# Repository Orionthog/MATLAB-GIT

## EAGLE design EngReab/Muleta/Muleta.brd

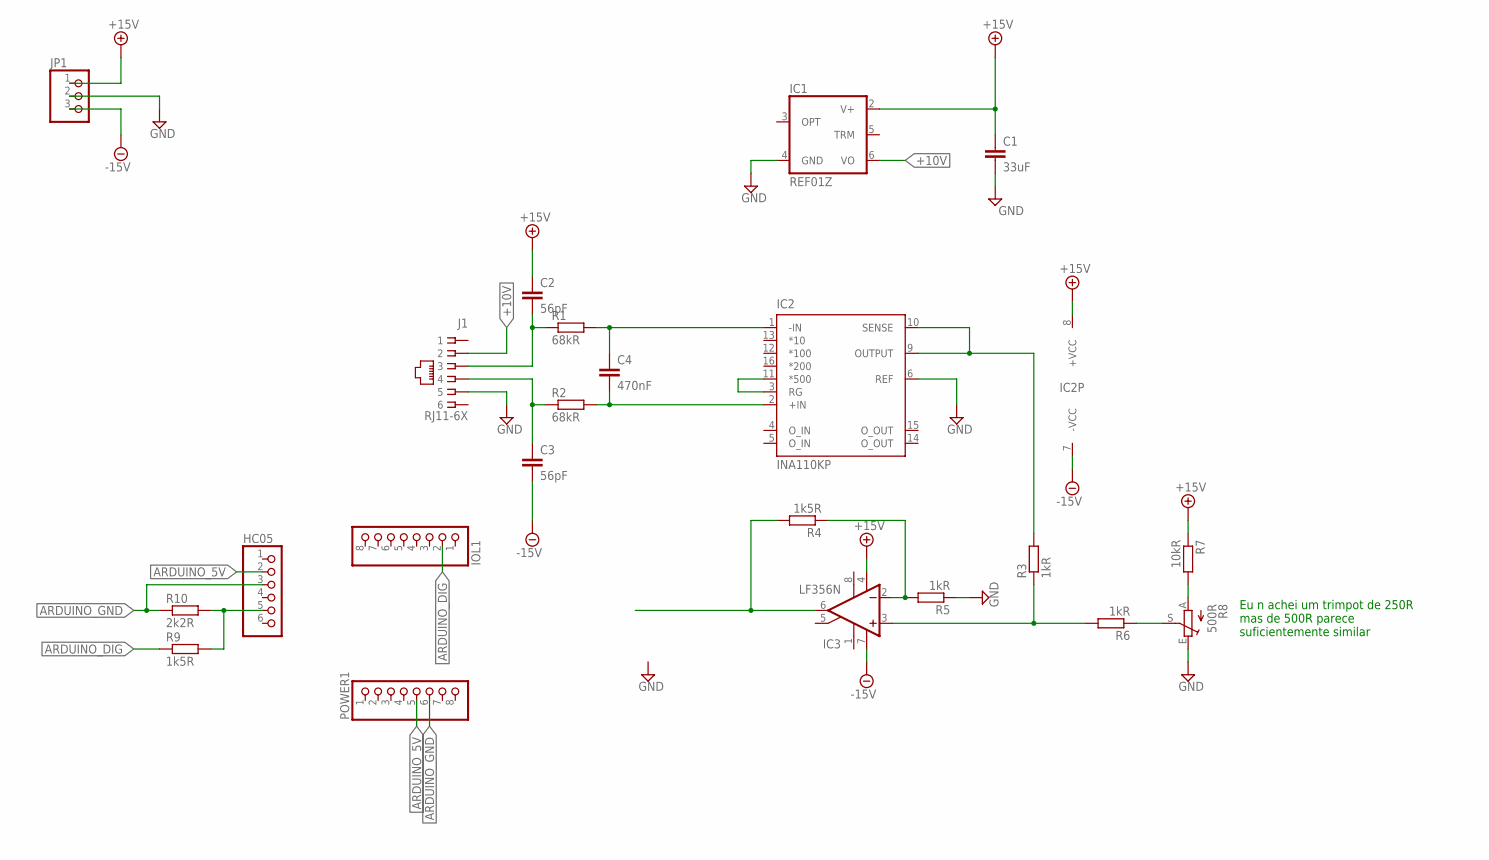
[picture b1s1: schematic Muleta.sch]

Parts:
C1: 33uF; C2.5-3
C2, C3: 56pF; C5B2.5
C4: 470nF; C5B2.5
HC05: PINHD-1X6/90; 1X06/90
IC1: REF01Z; DIL08
IC2: INA110KP; DIL16
IC3: LF356N; DIL08
IOL1: PINHD-1X8; 1X08
J1: RJ11-6X; RJ11-NO_SHIELD
JP1: PINHD-1X3; 1X03
POWER1: PINHD-1X8; 1X08
R1, R2: 68kR; 0207/7
R3, R5, R6: 1kR; 0207/7
R4, R9: 1k5R; 0207/7
R7: 10kR; 0207/7
R8: 500R; B64Y
R10: 2k2R; 0207/7

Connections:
+10V: IC1.6 (VO), J1.2
+15V: C1.1, C2.1, IC1.2 (V+), IC2.8 (+VCC), IC3.4 (V-), JP1.1, R7.1
-15V: C3.2, IC2.7 (-VCC), IC3.7 (V+), JP1.3
ARDUINO_5V: HC05.2, POWER1.5
ARDUINO_DIG: IOL1.2, R9.1
ARDUINO_GND: HC05.3, POWER1.6, R10.1
GND: C1.2, IC1.4 (GND), IC2.6 (REF), J1.5, JP1.2, R5.1, R8.E
unnamed: R6.1, R8.S
unnamed: R7.2, R8.A
unnamed: C3.1, J1.4, R2.1
unnamed: C2.2, J1.3, R1.1
unnamed: C4.2, IC2.2 (+IN), R2.2
unnamed: C4.1, IC2.1 (-IN), R1.2
unnamed: IC2.3 (RG), IC2.11 (*500)
unnamed: IC2.9 (OUTPUT), IC2.10 (SENSE), R3.2
unnamed: IC3.6 (OUT), R4.2
unnamed: IC3.2 (-IN), R4.1, R5.2
unnamed: IC3.3 (+IN), R3.1, R6.2
unnamed: HC05.5, R9.2, R10.2

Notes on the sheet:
Eu n achei um trimpot de 250R mas de 500R parece suficientemente similar

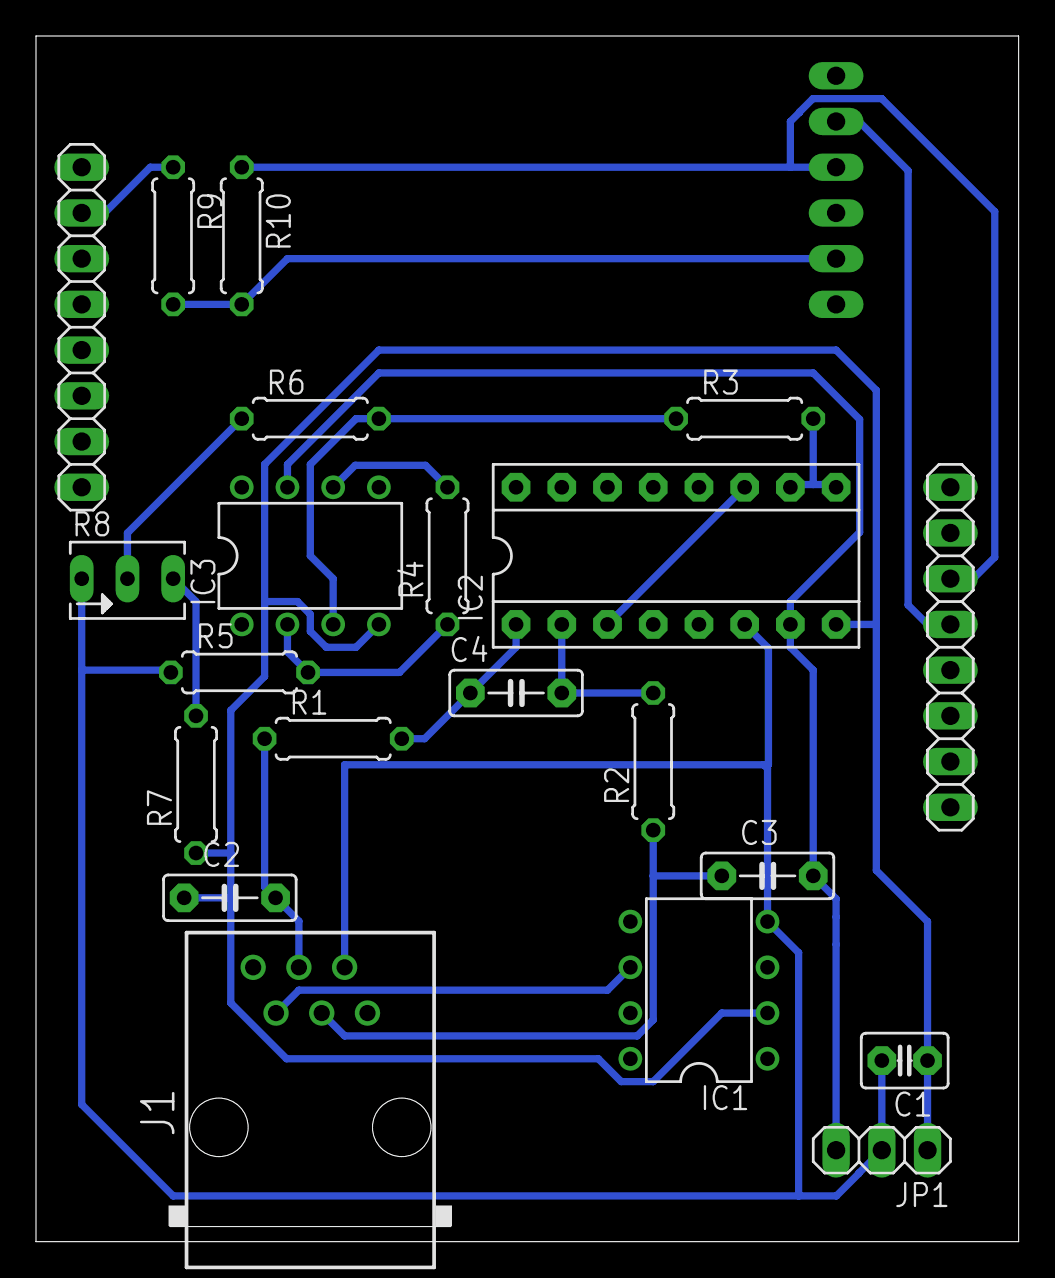
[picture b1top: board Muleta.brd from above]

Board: 2 copper layers, 54.6 x 67.0 mm, 22 parts (1 on the bottom side), 19 nets.

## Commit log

2018-04-02 Nada, ué
2018-04-02 MATLAB untill 02/04/18
2019-03-11 Create RobosManipuladores
2019-03-19 ainda sei dar commmit?
2019-03-25 Ae, carai. Consegui desenhar o cubo
2019-03-25 Uai, pq a pasta de controle desapareceu no github?
2019-03-25 Agora vai?
2019-03-25 Aula de hj deu bom :v
2019-03-30 Add files via upload
    oi
    denovooi
2019-03-30 agoravaia
2019-03-30 toma essa merda
2019-03-30 Add files via upload
    aaaaaaaaaaa
2019-03-30 eu sou o deus do terminal
2019-04-01 Add files via upload
    aaaaaaaaaaaaaaaaaaaaaaaah
2019-04-02 Reorganizando o rolê
2019-04-08 Sempre acreditei
2019-04-08 Add files via upload
    Tá dando bom
2019-04-08 Add files via upload
    Para de travaaaaaaaar
2019-04-19 Atualizando organização e labcontrole 1
2019-04-22 Nunca critiquei
2019-04-22 Removendo arquivo lixo .asv
2019-04-22 Agora funciona até no fedorao
2019-04-22 Pray for RAM
2019-04-22 Aaaaaah, eu vou swapar
2019-04-24 Mudando nome do repositório e adicionando projeto da muleta
2019-05-05 versão final do código
2019-05-13 UFalta corrigir o modelo 2c
2019-05-13 Atualizando caminho Fedora e comentando status.m
2019-05-13 Limpando dados desatualizados
2019-05-13 Atualizando versao da toolbox
2019-05-13 Ae, consertei o x
2019-05-19 Saida Analog A5?
2019-05-19 Adicionando arquivos experimento 2
2019-05-27 Parei no RPY
2019-05-27 Falta o 2E e o grafico do RPY
2019-05-29 Adicionando template bonitão de relatório
2019-06-03 Adicionando relatório no template chavoso com fonte chavosa
2019-06-03 Falta fazer o jacobiano
